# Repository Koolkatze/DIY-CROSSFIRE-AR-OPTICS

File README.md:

AR Optics can be made at home cheap and easy. 

I will use the highest F.O.V. you will be able to find in any place, no glasses use this fov for now, and DOUBLE MICRODISPLAY ON EACH EYE for this one.

DISCLAMER: The scale or size of the piezes can be modified with an even ratio, maybe the size of the display can vary for that same reason. I am still trying to figure out the best way to make the optics and its still not fisically mounted.

Experiment under your own financial risk.

List of products to build the project:

• The "LENS" is nothing but a transparent 6cm, 8cm, or 9cm diameter christmas ball (the focal point of the sphere is allways at its center so depending in which distance you would like to wear the glasses from the lens to the eyes you will want to choose one of them all, the best diameter afterall could be 9cm, remember: the lens will always need to be stuck ti the left limit of the diagram, that way you won't change the distance and angle of reflection, if you moved the lens to the right of the diagram for what ever reason you would overlap the images of the display) afterwards cut to 4,50cm diameter circle with a mini rotative electric saw or could also be same size transparent glass bulb cut with an electrically or gas heated metal wire and placed under cold water to break evenly as in the following video:

https://youtu.be/RjcmGEFi_NQ?si=239pzAycqYcrppN9

This is the type of christmas ball: https://es.aliexpress.com/item/1005007494654928.html?spm=a2g0o.productlist.main.11.74d5GHj1GHj1ru&algo_pvid=94ba693f-28a0-4506-ac77-2f596d9118a6&algo_exp_id=94ba693f-28a0-4506-ac77-2f596d9118a6-10&pdp_ext_f=%7B%22order%22%3A%2227%22%2C%22eval%22%3A%221%22%2C%22fromPage%22%3A%22search%22%7D&pdp_npi=6%40dis%21EUR%211.59%211.59%21%21%211.83%211.83%21%4021038e6617719419688692848e3321%2112000044592659945%21sea%21ES%213907980870%21X%211%210%21n_tag%3A-29919%3Bd%3Af6debfdc%3Bm03_new_user%3A-29895&curPageLogUid=5AtHR3SCXgeY&utparam-url=scene%3Asearch%7Cquery_from%3A%7Cx_object_id%3A1005007494654928%7C_p_origin_prod%3A

If you find a bulb with the same diameter, tell me, I want to add the option here.

You will need to cut the upper an bottom part of the 4,50cm circle, the measure between top and bottom is 2,5cm

It could be necessary to use some kind of glue, it's be best to use double grip tape to stick it to the holder.

• SUNGLASS OPTICS PROTECTOR AND EXTERNAL LIGHT DIMMER:

https://www.aliexpress.com/p/tesla-landing/index.html?scenario=c_ppc_item_bridge&productId=1005003310616806&_immersiveMode=true&withMainCard=true&src=google&aff_platform=true&isdl=y&src=google&albch=shopping&acnt=439-079-4345&isdl=y&slnk=&plac=&mtctp=&albbt=Google_7_shopping&aff_platform=google&aff_short_key=UneMJZVf&gclsrc=aw.ds&&albagn=888888&&ds_e_adid=&ds_e_matchtype=&ds_e_device=c&ds_e_network=x&ds_e_product_group_id=&ds_e_product_id=es1005003310616806&ds_e_product_merchant_id=109367859&ds_e_product_country=ES&ds_e_product_language=es&ds_e_product_channel=online&ds_e_product_store_id=&ds_url_v=2&albcp=21853428933&albag=&isSmbAutoCall=false&needSmbHouyi=false&gad_source=1&gad_campaignid=21853430043&gbraid=0AAAAACbpfvaWHlRZ_zBFrA5tYuxVPyeyF&gclid=Cj0KCQiAtfXMBhDzARIsAJ0jp3AHmM_JLUO1DJfEEb6c-dsZ-XLCHt6ay3dpdYcw2MYgSe6Cv_u7Ys8aAodBEALw_wcB

You will need to cut the lens to a WIDTH: 3,4cm, HEIGHT: 1,4cm.

It could be necessary to use some kind of glue, it's be best to use double grip tape to stick it to the holder.

• The "MIRROR" is nothing but any plane shiny transparent plastic or a semi-translucent mirror that covers from the top of the display from the top to the bottom of the display from the bottom.

• The microdisplay is this one: 
 
https://www.alibaba.com/product-detail/1-1-Inch-High-Resolution-Bar_1601580211595.html?spm=a2700.galleryofferlist.normal_offer.d_title.697913a01LHWSC&priceId=52afbaf441e749009b5a6feb538b42e2

• The "OPTICS HOLDER", a 3D Printed model that holds the optics when you press the holder inside the frames of the glasses.

• The "FRAME" is a 3D printable model able to hold the optics holder and the optics stuck by applying pressure. 

• The optics rear protector, it can be any transparent material, a glass, cut by WIDTH 4,6cm X HEIGHT 5,1cm and rounded by the corners.

• The "TEMPLES" are 3D printed and hold the electronics of the project, for now I have done a PCB that should act as an image splitter to divide up and down image
and it´s slave PCB to act as a slave and do the same (I STILL NEED TO VERIFY IT WORKS AS I HAVE TO RECIEVE IT FROM JLCPCB).

ROADMAP:

1. FIND A HIGH RESOLUTION MICRODISPLAY THAT FITS THE DESIGN. ✅ done (FOUND THE BEST RESOLUTION).
   
2. CREATE A 3D PRINTABLE MODEL OF THE CASE FOR THE OPTICS (TO PLACE THE DISPLAY, LENS AND MIRROR IN IT AND HIDE ANY CABLE). ✅ done

3. CREATE A 3D GLASSES FRAME MODEL FOR THE OPTICS TO SIT ON YOUR FACE. ✅ done

4. CREATE A 3D MODEL FOR THE TEMPLES THAT HOLDS THE ELECTRONICS FOR THE DISPLAYS TO WORK. W.I.P (Still need to try if the temples hold well the elecronics).

5. WE WILL HAVE TO DECIDE IF THEY WILL BE STANDALONE OR TETHERED AND TREAT THE SOFTWARE AS WE NEED.
6. CREATE AN EXTERNAL SOLUTION FOR BATTERY CAPACITY, TO TRY AND EXTEND BATTERY DURING LONG PERIODS OF TIME WHILE IN USE.
7. CREATE DIFFERENT DESIGNS FOR FASHIONABLE AR GLASSES.

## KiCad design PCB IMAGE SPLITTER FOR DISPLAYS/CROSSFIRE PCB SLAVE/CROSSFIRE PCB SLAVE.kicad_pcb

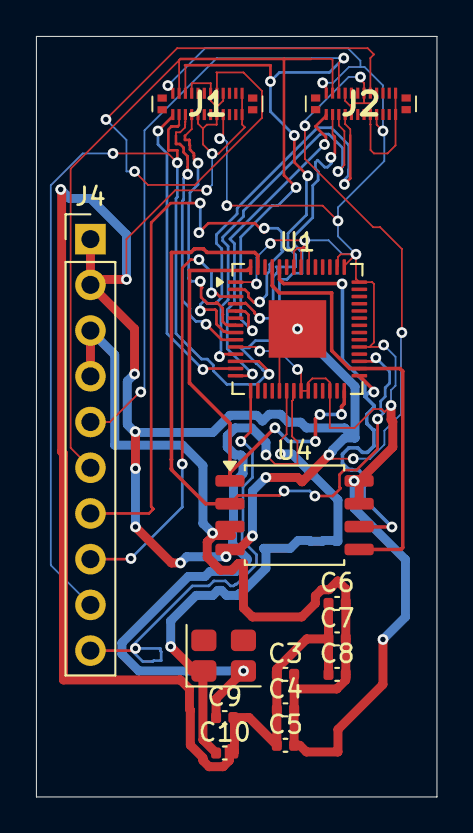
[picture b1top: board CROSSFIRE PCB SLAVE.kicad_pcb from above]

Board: 2 copper layers, 22.2 x 42.2 mm, 14 parts (0 on the bottom side), 21 nets.

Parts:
C3, C4, C5, C6: 100nF; C_0402_1005Metric
C7: 10uF; C_0402_1005Metric
C8: C; C_0402_1005Metric
C9, C10: 12pF; C_0402_1005Metric
J1, J2: Conn_02x12_Odd_Even; BM28B0624DP2035V51
J4: Conn_01x10; PinHeader_1x10_P2.54mm_Vertical
U1: RP2040; QFN-56-1EP_7x7mm_P0.4mm_EP3.2x3.2mm
U4: W25Q16JVSS; SOIC-8_5.3x5.3mm_P1.27mm
Y1: 12MHz; Crystal_SMD_3225-4Pin_3.2x2.5mm

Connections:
+1V8: J1.16, J2.16
+3.3V: C3.2, C4.2, C5.2, C6.2, C7.2, C8.2, J1.2, J1.17, J2.2, J2.17, J4.3, J4.4, U1.1 (IOVDD), U1.10 (IOVDD), U1.22 (IOVDD), U1.23 (DVDD), U1.26 (RUN), U1.33 (IOVDD), U1.42 (IOVDD), U1.43 (ADC_AVDD), U1.44 (VREG_VIN), U1.48 (USB_VDD), U1.49 (IOVDD), U1.50 (DVDD), U4.3 (~WP/IO_{2}), U4.7 (~HOLD/~RESET/IO_{3}), U4.8 (VCC)
/CS_BOT: J2.7, U1.8 (GPIO6)
/CS_TOP: J1.7, U1.7 (GPIO5)
/DCX_BOT: J2.5, U1.11 (GPIO8)
/DCX_TOP: J1.5, U1.9 (GPIO7)
/FLASH_CLK: U1.29 (GPIO18), U1.52 (QSPI_SCLK), U4.6 (CLK)
/FLASH_CS: U1.28 (GPIO17), U1.56 (~QSPI_SS), U4.1 (~CS)
/FLASH_MISO: U1.31 (GPIO20), U1.55 (QSPI_SD1), U4.2 (DO/IO_{1})
/FLASH_MOSI: U1.30 (GPIO19), U1.53 (QSPI_SD0), U4.5 (DI/IO_{0})
/MOSI: J1.4, J2.4, J4.6, U1.5 (GPIO3)
/RST: J1.3, J2.3, J4.9, U1.12 (GPIO9)
/SCL: J1.6, J2.6, J4.5, U1.4 (GPIO2)
/TE_BOT: J2.1, U1.14 (GPIO11)
/TE_TOP: J1.1, U1.13 (GPIO10)
/UART_RX: J4.8, U1.3 (GPIO1)
/UART_TX: J4.7, U1.2 (GPIO0)
/VSYNC: J4.10, U1.15 (GPIO12)
GND: C3.1, C4.1, C5.1, C6.1, C7.1, C8.1, C9.2, C10.2, J1.8, J1.9, J1.14, J1.15, J1.18, J1.23, J1.24, J2.8, J2.9, J2.14, J2.15, J2.18, J2.23, J2.24, J4.1, J4.2, U1.19 (TESTEN), U1.57 (GND), U4.4 (GND)
unnamed: C10.1, U1.20 (XIN), Y1.1
unnamed: C9.1, U1.21 (XOUT), Y1.2

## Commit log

2026-02-20 SCHEMA
    Here I show the ray tracing schema of the AR optics.
2026-02-20 Add instructions for making AR optics
    Added basic information on creating AR optics at home.
2026-02-20 Enhance README with details on AR optics project
    Expanded on the description of AR optics construction.
2026-02-20 Fix spelling error in README.md
    Corrected spelling of 'HICHEST' to 'HIGHEST' in the README.
2026-02-20 Correct description of mirror material in README
2026-02-20 Add roadmap for project development
    Added a roadmap outlining the development steps for the project.
2026-02-20 Update README with product list and corrections
    Corrected typos and improved clarity in the README. Added a list of products needed for the project and detailed specifications for components.
2026-02-20 Fix typo in README.md
2026-02-20 Enhance README with more details on AR optics
    Expanded the description of AR optics to include details about F.O.V. usage.
2026-02-20 Update LENS description with correct diameter
2026-02-20 Update 'LENS' product description in README
    Expanded description of the 'LENS' product to include alternative methods of creation.
2026-02-20 Fix typo in MIRROR description in README.md
2026-02-20 Update roadmap with completed microdisplay task
2026-02-20 Revise microdisplay roadmap item with future plans
    Updated the roadmap item for the microdisplay with additional details about future improvements.
2026-02-20 Fix grammar in roadmap item about microdisplay resolution
    Corrected a grammatical error in the roadmap section regarding the resolution of the microdisplay.
2026-02-20 Update README with project details and disclaimer
    Added disclaimer and project overview to README.
2026-02-20 Revise microdisplay specifications in README
    Updated specifications and improved clarity of the microdisplay description.
2026-02-20 Update AMOLED microdisplay description with link
    Added a link to the AMOLED microdisplay for reference.
2026-02-21 Update 'LENS' description for clarity
    Clarified the description of the 'LENS' in the README.
2026-02-22 Update 'LENS' description and add video link
    Clarified the description of the 'LENS' and added a reference video.
2026-02-22 Update README with new tasks for AR glasses project
    Added additional tasks for creating AR glasses.
2026-02-23 Revise microdisplay details and roadmap steps
    Updated microdisplay specifications and roadmap items for clarity.
2026-02-24 Update README with new product links and roadmap status
    Added links for sunglasses optics protector and external light dimmer to the README.
2026-02-24 Added a STL showing the 3D holder for the optics.
    the 3D representation of the optics
2026-02-24 This is the printable holder
    3D model of the holder to send for 3D printing.
2026-02-24 UPLOADED MIRROR POSITION
    Had to adjust mirror for the blueprint.
2026-02-24 Corrected Upload
2026-02-24 Update README with lens cutting instructions and materials
    Added detailed instructions for lens cutting and materials needed for the project.
2026-02-24 Update README with christmas ball purchase link
    Added links for purchasing the christmas ball and requested user input for bulb options.
2026-02-24 frame for optics
    this is an example you can use the printable in the next file
2026-02-24 This is a printable frame for the optics
    this frame can hold the holder inside and keep it stuck with only applying pressure.
2026-02-24 Update roadmap and add details for 3D models
2026-02-24 Update README with clearer AR optics description
    Clarified the description of AR optics and added details about the double microdisplay.
2026-02-24 UPDATED FILES
    Now it closes better on the front part between the sunglasse and the frame.
2026-02-24 Small revision.
    A little thickness edit.
2026-02-24 Update README with link to FRAME STL file
    Added a link to the 3D printable FRAME file in the README.
2026-02-24 BEST QUALITY 3D FRAME
    Made some changes to fit better quality model.
2026-02-24 DIVIDED MODEL TO PRINT BY PARTS
    EACH PRITABLE PART NOW IS SET ON AN INDIVIDUAL STL FILE
2026-02-24 added folder
    FOLDER TO ORGANIZE
2026-02-24 Update status of 3D model for temples in README
    Updated the status of the 3D model for the temples to indicate it's a work in progress and added a note about testing electronics fit.
2026-02-24 Enhance README with image and introductory details
    Added an image and expanded the introduction about AR optics.
2026-02-25 BETTER MESH
2026-03-03 Make image link in README clickable
    Updated image link in README to be clickable and point to the raw image.
2026-03-03 Fix image link formatting in README
    Updated image link formatting in README.md.
2026-03-03 Fix image link and improve README formatting
    Updated image link and fixed formatting issues in README.
2026-03-03 Update README with product list and new images
    Added a list of products needed for the project and updated images.
2026-03-03 stl update
2026-03-09 mesh update
2026-03-09 PCB IMAGE SPLITTER
2026-03-09 Revise README for optics project details
    Updated descriptions for the 'TEMPLES' and removed outdated links.
